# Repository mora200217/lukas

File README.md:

# Lukas: Linked Unit for Kinematic Artistic Sketching
Manipulador 2R dibuja treboles

## Getting Started 
El repo está desarrollado en Julia - un Lenguaje de programación moderno y científico. Para poder usarlo, recomendamos instalar Julia v1.11 y la extension de Julia a VSC 

```
  julia
  ]
  activate .
```

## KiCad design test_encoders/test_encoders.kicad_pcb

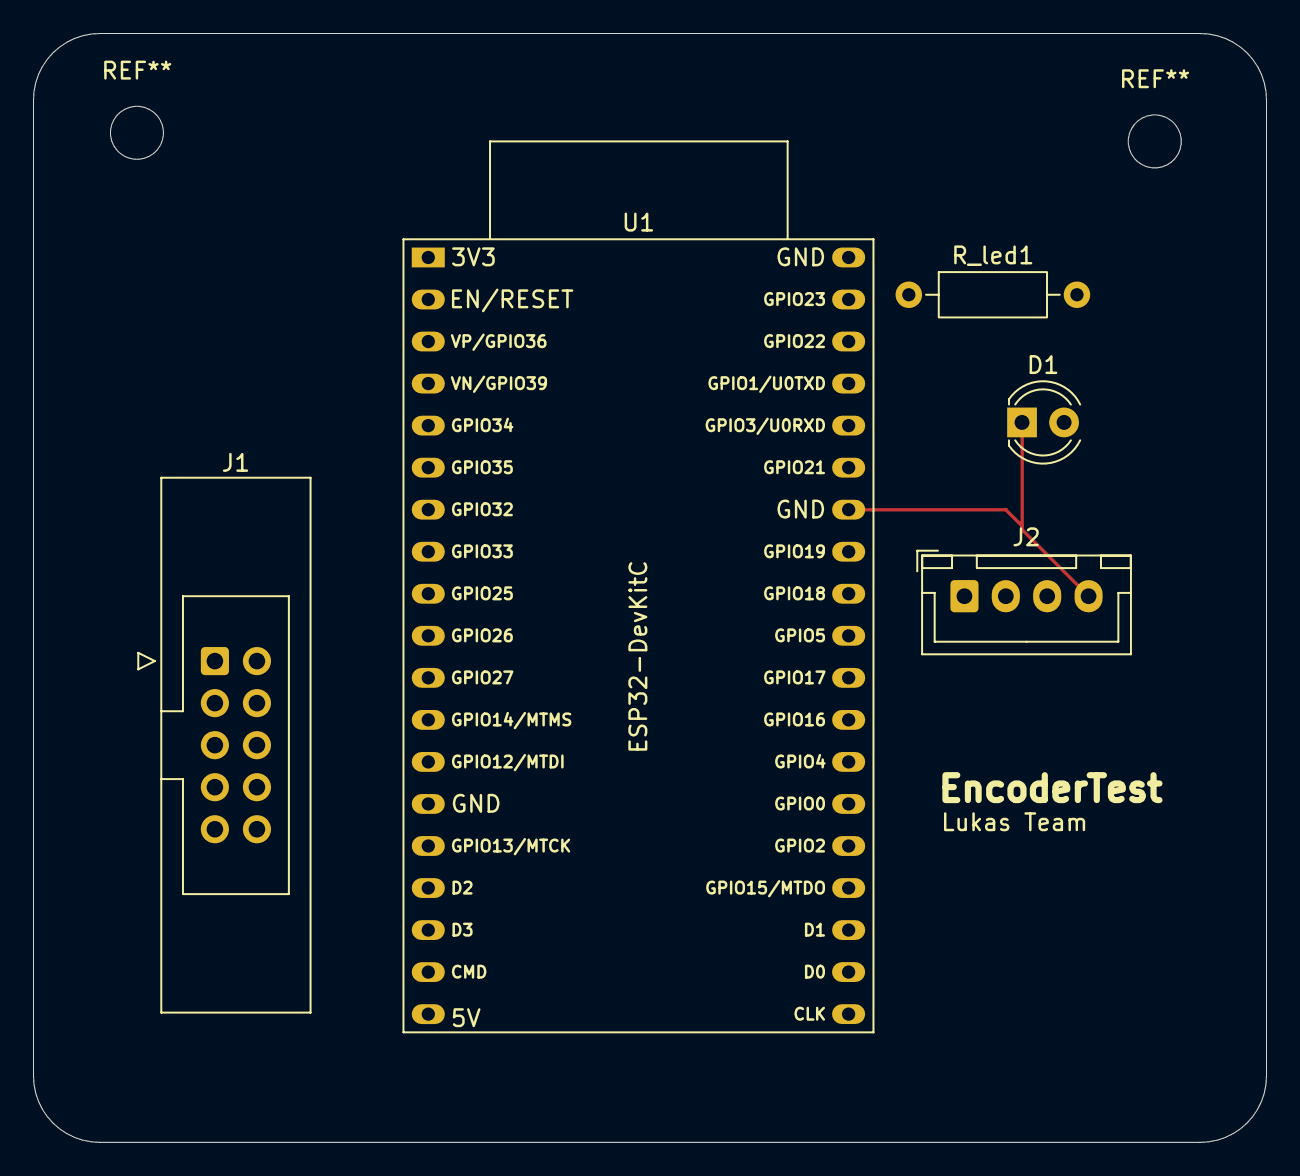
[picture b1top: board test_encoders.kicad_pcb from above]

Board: 2 copper layers, 74.5 x 67.0 mm, 5 parts (0 on the bottom side), 9 nets.

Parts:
D1: LED; LED_D4.0mm
J1: DIN; IDC-Header_2x05_P2.54mm_Latch_Vertical
J2: Conn_01x04_Socket; JST_XH_B4B-XH-A_1x04_P2.50mm_Vertical
R_led1: 220; R_Axial_DIN0207_L6.3mm_D2.5mm_P10.16mm_Horizontal
U1: ESP32-DevKitC

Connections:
+5V: J1.2, J2.1, R_led1.1, U1.19 (5V)
/A+: J1.6, U1.31 (GPIO19)
/A-: J1.5, U1.33 (GPIO21)
/B+: J1.8, U1.36 (GPIO22)
/B-: J1.7, U1.37 (GPIO23)
/Z+: J1.10, U1.9 (DAC_1/ADC2_CH8/GPIO25)
/Z-: J1.9, U1.10 (DAC_2/ADC2_CH9/GPIO26)
GND: D1.1 (K), J1.3, J2.4, U1.14 (GND), U1.32 (GND), U1.38 (GND)
unnamed: D1.2 (A), R_led1.2

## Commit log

2025-09-04 [Update] Project structure and a2R
2025-09-23 [Update] base
2025-09-25 [test]
2025-09-26 Update Project Name
2025-10-01 [Update] folder remove
2025-10-01 [Update] Directorios
2025-10-01 [UPDATE]
2025-10-02 parametrization_V2, GUI, jl
2025-10-02 [Update] Files new test and docs
2025-10-03 Julia GUI for Param (interactiv), missing animaton
2025-10-03 chore: ignore local backups of main.jl
2025-10-03 OptimizationCodes
2025-10-03 ActOptCode
2025-10-03 [Update] obj function
2025-10-03 NewObjectiveFunction
2025-10-03 CodigoWorkspaceTrayectoria
2025-10-03 [Update] sim
2025-10-03 Param eq un GUI | Final
2025-10-03 [Update] images optimization
2025-10-03 cinematica
2025-10-03 Param Gui, Final
2025-10-03 [Update] Sim params update
2025-10-04 Param & Kinem complet in an unique module
2025-10-06 Complete Calcs Module: Param + Kinem (Live)
2025-10-06 Update Optimization correction
2025-10-06 Opti
2025-10-08 CodigoModificarBrazosInteractivo
2025-10-29 PruebaArduinoEncoderMaxon
2025-10-30 ArchivosArduion
2025-10-31 [Update] Julia changes for modules. Lagrangian formulation in torques calculator. Matlab model for DC motor
2025-11-04 L1MayorA25
2025-11-05 [New] Simscape model
2025-11-05 CodigosArduino
2025-11-05 UPDATE [Lagrange model for modeling torque]
2025-11-05 Restore test/symbolics_test.jl from origin/dev (drop local rename)
2025-11-06 [Update] SLX
2025-11-06 [Update] ROS2
2025-11-06 [Update] Test for ESP Embedded
2025-11-06 CambiosArduino
2025-11-13 [Update] Robot descriptoin Lukas pkg
2025-11-13 [Udpate Oscar]
2025-11-14 LibreriaEncodersMotores
2025-11-14 PruebaLibreria
2025-11-15 CorrecionLibreria
2025-11-19 comentarios Prueba.jl
2025-11-19 Update Libreria
2025-11-19 [Checkpoint] functional interface
2025-11-20 Refactor EncodersMotores.h with new definitions
    Added motor control pins, parameters, and public API functions.
2025-11-21 [Update] Info
2025-11-21 [Update] control test encoder
2025-11-21 ¨Test~
2025-11-21 [Update] prueba
